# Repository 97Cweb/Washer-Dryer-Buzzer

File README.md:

# Washer-Dryer-Buzzer
An Arduino project based on adding a buzzer to a washer and dryer on the same board

This project uses the following schematic:

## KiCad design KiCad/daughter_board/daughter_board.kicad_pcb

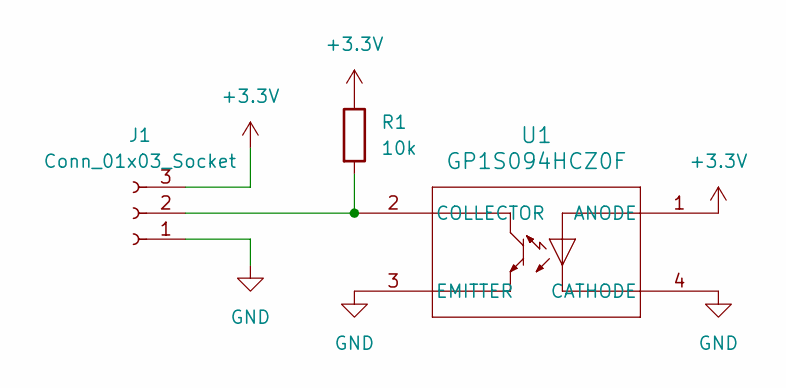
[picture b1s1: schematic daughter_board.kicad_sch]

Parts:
J1: Conn_01x03_Socket; JST_XA_B03B-XASK-1_1x03_P2.50mm_Vertical
R1: 10k; R_1206_3216Metric_Pad1.30x1.75mm_HandSolder
U1: GP1S094HCZ0F; TO_4HCZ0F_SHP

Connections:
+3.3V: J1.3, R1.1, U1.1 (ANODE)
GND: J1.1, U1.3 (EMITTER), U1.4 (CATHODE)
unnamed: J1.2, R1.2, U1.2 (COLLECTOR)

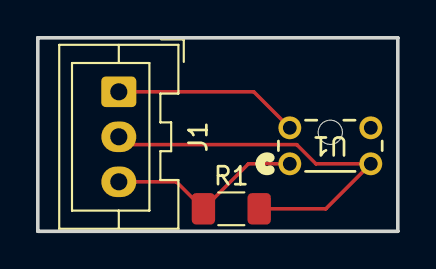
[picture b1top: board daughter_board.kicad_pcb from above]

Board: 2 copper layers, 20.0 x 10.8 mm, 3 parts (0 on the bottom side), 3 nets.

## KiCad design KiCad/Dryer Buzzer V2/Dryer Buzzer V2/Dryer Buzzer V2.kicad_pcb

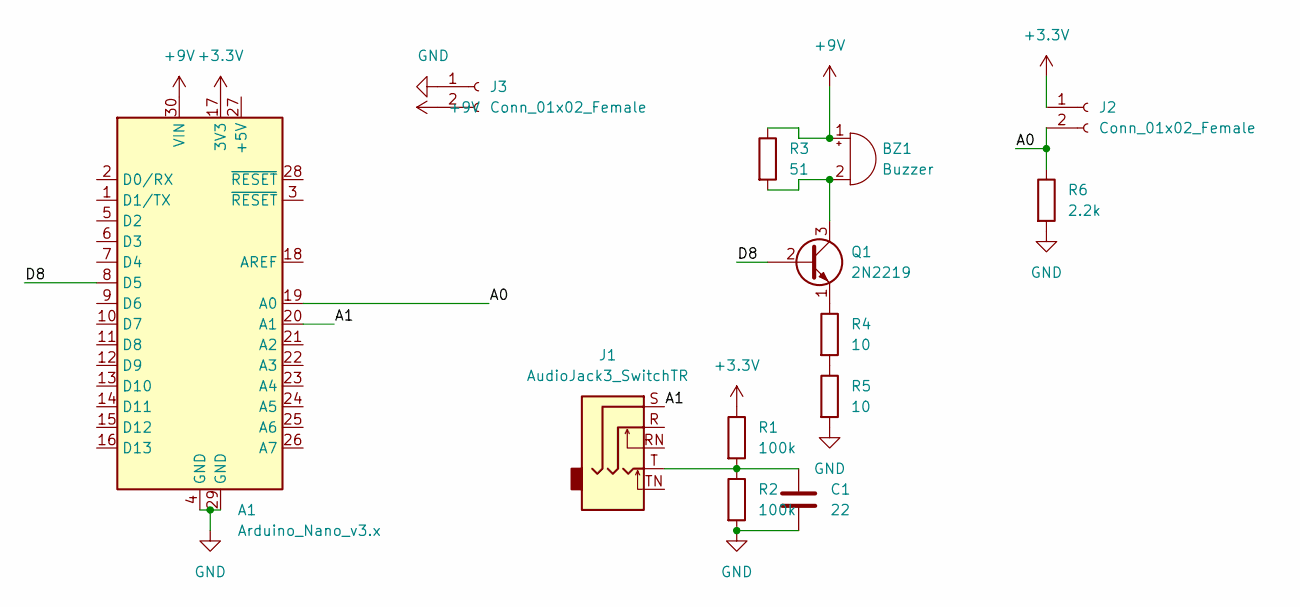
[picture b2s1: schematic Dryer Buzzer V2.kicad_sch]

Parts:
A1: Arduino_Nano_v3.x; Arduino_Nano
BZ1: Buzzer; Buzzer_12x9.5RM7.6
C1: 22; CP_Radial_D5.0mm_P2.50mm
J1: AudioJack3_SwitchTR; Jack_3.5mm_CUI_SJ1-3525N_Horizontal
J2, J3: Conn_01x02_Female; JST_EH_B2B-EH-A_1x02_P2.50mm_Vertical
Q1: 2N2219; TO-39-3
R1, R2: 100k; R_Axial_DIN0207_L6.3mm_D2.5mm_P10.16mm_Horizontal
R3: 51; R_Axial_DIN0207_L6.3mm_D2.5mm_P10.16mm_Horizontal
R4, R5: 10; R_Axial_DIN0207_L6.3mm_D2.5mm_P10.16mm_Horizontal
R6: 2.2k; R_Axial_DIN0207_L6.3mm_D2.5mm_P10.16mm_Horizontal

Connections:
+3V3: A1.17 (3V3), J2.1, R1.1
+9V: A1.30 (VIN), BZ1.1 (-), J3.2, R3.1
/A0: A1.19 (A0), J2.2, R6.1
/A1: A1.20 (A1), J1.S
/D8: A1.8 (D5), Q1.2 (B)
GND: A1.4 (GND), A1.29 (GND), C1.2, J3.1, R2.2, R5.2, R6.2
unnamed: BZ1.2 (+), Q1.3 (C), R3.2
unnamed: C1.1, J1.T, R1.2, R2.1
unnamed: Q1.1 (E), R4.1
unnamed: R4.2, R5.1

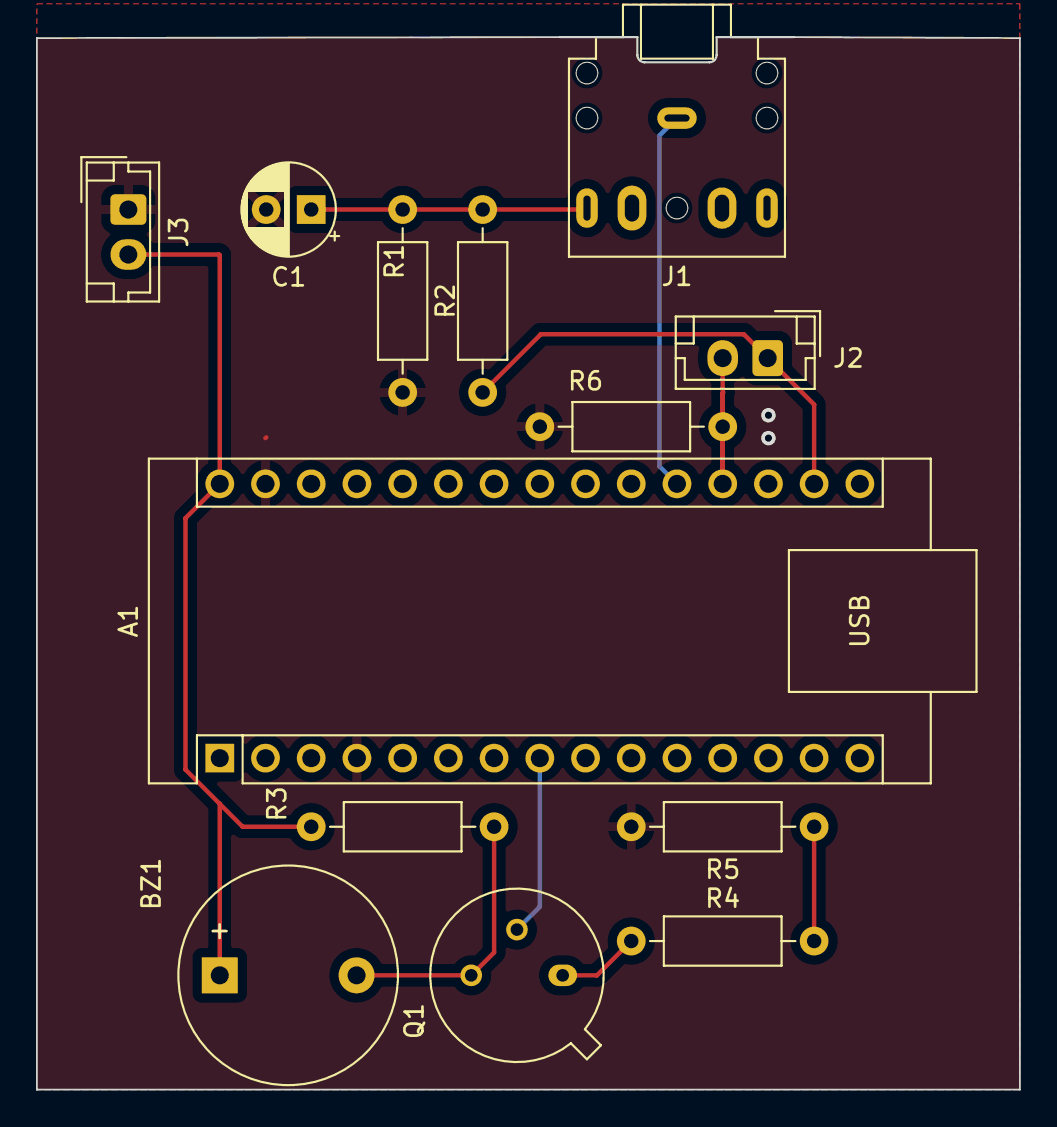
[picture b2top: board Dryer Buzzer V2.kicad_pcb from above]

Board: 2 copper layers, 54.6 x 58.5 mm, 13 parts (0 on the bottom side), 10 nets.

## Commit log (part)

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2024-08-09 update remove lowpower mode lower dryer threshold
